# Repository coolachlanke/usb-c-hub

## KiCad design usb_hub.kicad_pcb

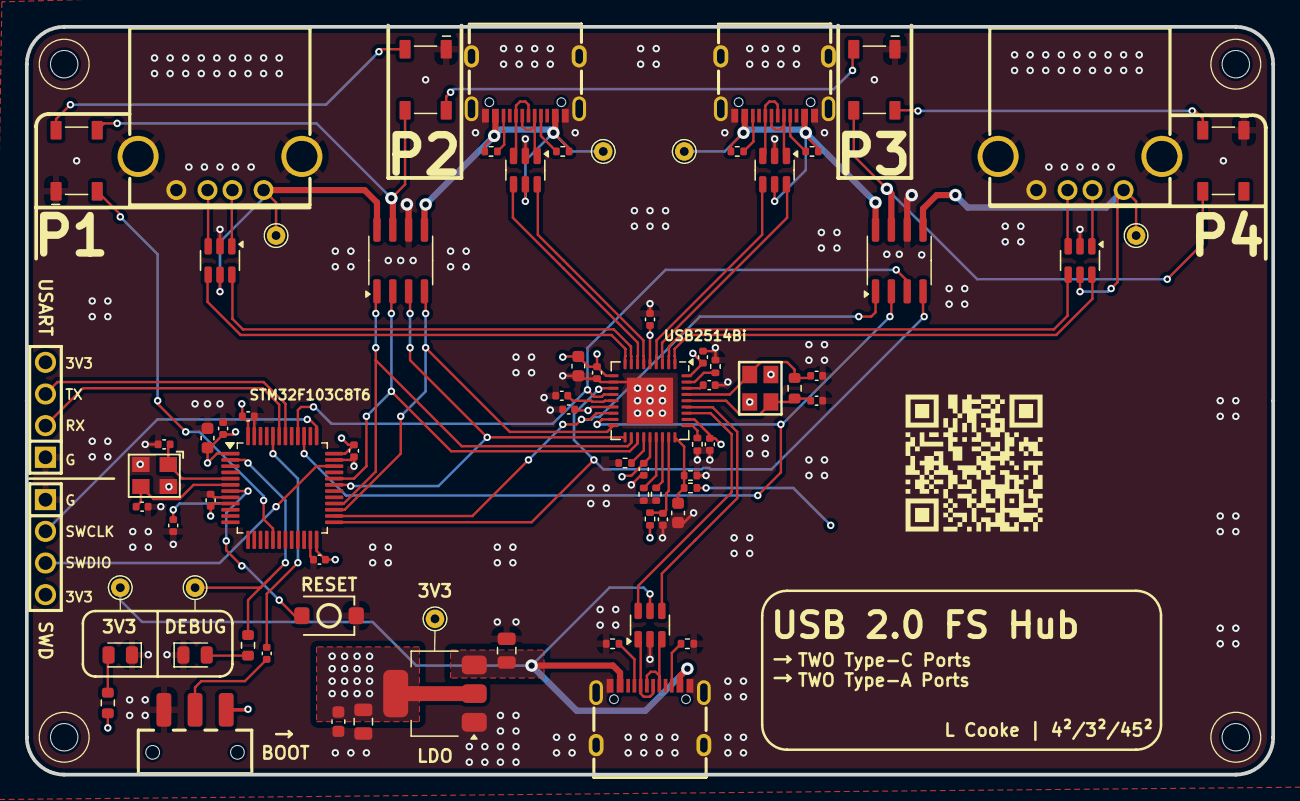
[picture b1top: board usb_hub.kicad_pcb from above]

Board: 4 copper layers, 100.0 x 60.0 mm, 81 parts (0 on the bottom side), 68 nets.

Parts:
C1: 100n; C_0603_1608Metric
C2, C10: 18p; C_0402_1005Metric
C3, C4, C5, C6, C9, C11, C14, C16, C17, C18, C19, C20, C21, C22, C23: 100n; C_0402_1005Metric
C7, C8: 1u; C_0603_1608Metric
C12, C13: 22u; C_0805_2012Metric
C15: 10u; C_0603_1608Metric
C24, C25: 10p; C_0402_1005Metric
D1: GREEN; LED_0805_2012Metric
D2: YELLOW; LED_0805_2012Metric
D3, D4, D5, D6: WS2812B; LED_WS2812B_PLCC4_5.0x5.0mm_P3.2mm
H1, H2, H3, H4: MountingHole; MountingHole_2.2mm_M2
J1, J2, J3: USB_C_Receptacle_USB2.0_16P; USB-C-SMD_TYPE-C-6PIN-2MD-073
J4, J5: USB_A; USB-A-TH_USB-231-ARY
J7, J8: Conn_01x04_Pin; HDR-TH_4P-P2.54-V-M
R1, R2: 5.1k; R_0402_1005Metric
R3, R8, R12, R13: 56k; R_0402_1005Metric
R4, R6, R7, R11, R14, R15, R16: 100k; R_0402_1005Metric
R5: 750R; R_0603_1608Metric
R9: 1M; R_0603_1608Metric
R10: 12k; R_0402_1005Metric
R17: 10k; C_0402_1005Metric
R18: 1k; R_0603_1608Metric
SW1: SW_SPDT; SW-SMD_K3-1280S-K1
SW2: SW_Push; SW-SMD_L3.9-W3.0-P4.45
TP1, TP2, TP3, TP4, TP5, TP6, TP7: TestPoint; TestPoint_THTPad_D1.5mm_Drill0.7mm
U1: USB2514B_Bi; QFN-36-1EP_6x6mm_P0.5mm_EP3.7x3.7mm
U2: AMS1117-3.3; SOT-223-3_TabPin2
U3, U4, U5, U6, U8: USBLC6-2SC6; SOT-23-6
U7, U9: MIC2026-1YM; SOIC-8_3.9x4.9mm_P1.27mm
U10: STM32F103C8T6; LQFP-48_7x7mm_P0.5mm
Y1: 24MHz; CRYSTAL-SMD_4P-L3.2-W2.5-BL_SIT8008BI
Y2: 16MHz; OSC-SMD_4P-L3.2-W2.5-BL

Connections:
+3V3: C1.1, C3.1, C4.1, C5.1, C6.1, C7.1, C13.1, C15.1, C16.1, C17.1, C18.1, C19.1, C20.1, C21.1, C22.1, J7.4, J8.4, R5.1, R11.2, SW1.1 (A), TP2.1, U1.5 (VDDA33), U1.10 (VDDA33), U1.15 (VDD33), U1.23 (VDD33), U1.29 (VDDA33), U1.36 (VDDA33), U2.2 (VO), U10.1 (VBAT), U10.9 (VDDA), U10.24 (VDD), U10.36 (VDD), U10.48 (VDD)
/BOOT0: R17.2, U10.44 (BOOT0)
/DEBUG: R18.1, TP5.1, U10.2 (PC13)
/DEBUG_LED: D2.2 (A), R18.2
/DOWN_1_D+: U1.2 (USBDP_DN1/PRT_DIS_P1), U8.4 (I/O2)
/DOWN_1_D-: U1.1 (USBDM_DN1/PRT_DIS_M1), U8.6 (I/O1)
/DOWN_2_D+: U1.4 (USBDP_DN2/PRT_DIS_P2), U5.4 (I/O2)
/DOWN_2_D-: U1.3 (USBDM_DN2/PRT_DIS_M2), U5.6 (I/O1)
/DOWN_3_D+: U1.7 (USBDP_DN3/PRT_DIS_P3), U4.4 (I/O2)
/DOWN_3_D-: U1.6 (USBDM_DN3/PRT_DIS_M3), U4.6 (I/O1)
/DOWN_4_D+: U1.9 (USBDP_DN4/PRT_DIS_P4), U6.4 (I/O2)
/DOWN_4_D-: U1.8 (USBDM_DN4/PRT_DIS_M4), U6.6 (I/O1)
/EN1: U1.12 (PRTPWR1/BC_EN1), U7.4 (ENB), U10.25 (PB12)
/EN2: U1.16 (PRTPWR2/BC_EN2), U7.1 (ENA), U10.26 (PB13)
/EN3: U1.18 (PRTPWR3/BC_EN3), U9.4 (ENB), U10.27 (PB14)
/EN4: U1.20 (PRTPWR4/BC_EN4), U9.1 (ENA), U10.28 (PB15)
/HSE_IN: C24.1, U10.5 (PD0), Y2.1
/HSE_OUT: C25.1, U10.6 (PD1), Y2.3
/LED_DATA: D3.4 (DIN), U10.17 (PA7)
/NRST: C23.1, SW2.2, U10.7 (NRST)
/OCS_N1: U1.13 (OCS_N1), U7.3 (FLGB), U10.40 (PB4)
/OCS_N2: U1.17 (OCS_N2), U7.2 (FLGA), U10.39 (PB3)
/OCS_N3: U1.19 (OCS_N3), U9.3 (FLGB), U10.31 (PA10)
/OCS_N4: U1.21 (OCS_N4), U9.2 (FLGA), U10.32 (PA11)
/PWR_LED: D1.2 (A), R5.2
/SWCLK: J8.2, U10.37 (PA14)
/SWDIO: J8.3, U10.34 (PA13)
/SW_BOOT0: R17.1, SW1.2 (B)
/UP_D+: U1.31 (USBDP_UP), U3.4 (I/O2)
/UP_D-: U1.30 (USBDM_UP), U3.6 (I/O1)
/USART_RX: J7.2, U10.43 (PB7)
/USART_TX: J7.3, U10.42 (PB6)
GND: C1.2, C2.2, C3.2, C4.2, C5.2, C6.2, C7.2, C8.2, C9.2, C10.2, C11.2, C12.2, C13.2, C14.2, C15.2, C16.2, C17.2, C18.2, C19.2, C20.2, C21.2, C22.2, C23.2, C24.2, C25.2, D1.1 (K), D2.1 (K), D3.3 (VSS), D4.3 (VSS), D5.3 (VSS), D6.3 (VSS), J1.A1 (GND), J1.S1 (SHIELD), J2.A1 (GND), J2.S1 (SHIELD), J3.A1 (GND), J3.S1 (SHIELD), J4.4 (GND), J4.5 (Shield), J5.4 (GND), J5.5 (Shield), J7.1, J8.1, R1.2, R2.2, R4.1, R6.1, R10.1, R14.1, R15.1, R16.1, SW1.3 (C), SW2.1, U1.11 (TEST), U1.37 (VSS), U2.1 (GND), U3.2 (GND), U4.2 (GND), U5.2 (GND), U6.2 (GND), U7.6 (GND), U8.2 (GND), U9.6 (GND), U10.8 (VSSA), U10.23 (VSS), U10.35 (VSS), U10.47 (VSS), Y1.2, Y1.4, Y2.2, Y2.4
unnamed: D3.2 (DOUT), D4.4 (DIN)
unnamed: D4.2 (DOUT), D5.4 (DIN)
unnamed: D5.2 (DOUT), D6.4 (DIN)
unnamed: J1.A5 (CC1), R1.1
unnamed: J1.B5 (CC2), R2.1
unnamed: J1.A6 (D+), J1.B6 (D+), U3.3 (I/O2)
unnamed: J1.A7 (D-), J1.B7 (D-), U3.1 (I/O1)
unnamed: J2.A5 (CC1), R12.1
unnamed: J2.B5 (CC2), R13.1
unnamed: J2.A6 (D+), J2.B6 (D+), U4.3 (I/O2)
unnamed: J2.A7 (D-), J2.B7 (D-), U4.1 (I/O1)
unnamed: J3.A5 (CC1), R3.1
unnamed: J3.B5 (CC2), R8.1
unnamed: J3.A6 (D+), J3.B6 (D+), U5.3 (I/O2)
unnamed: J3.A7 (D-), J3.B7 (D-), U5.1 (I/O1)
unnamed: J4.3 (D+), U6.3 (I/O2)
unnamed: J4.2 (D-), U6.1 (I/O1)
unnamed: J5.3 (D+), U8.3 (I/O2)
unnamed: J5.2 (D-), U8.1 (I/O1)
unnamed: C11.1, U1.14 (CRFILT)
unnamed: R4.2, U1.25 (HS_IND/CFG_SEL1)
unnamed: C9.1, U1.34 (PLLFILT)
unnamed: R10.2, U1.35 (RBIAS)
unnamed: C14.1, R11.1, U1.26 (RESET_N)
unnamed: R16.2, U1.24 (SCL/SMBCLK/CFG_SEL0)
unnamed: R15.2, U1.22 (SDA/SMBDATA/NON_REM1)
unnamed: R14.2, U1.28 (SUSP_IND/LOCAL_PWR/NON_REM0)
unnamed: C8.1, R6.2, R7.1, U1.27 (VBUS_DET)
unnamed: C10.1, R9.2, U1.33 (XTALIN/CLKIN), Y1.1
unnamed: C2.1, R9.1, U1.32 (XTALOUT), Y1.3
VBUS: C12.1, D3.1 (VDD), D4.1 (VDD), D5.1 (VDD), D6.1 (VDD), J1.A4 (VBUS), R7.2, TP1.1, U2.3 (VI), U3.5 (VBUS), U7.7 (IN), U9.7 (IN)
VBUS_1: J5.1 (VBUS), TP7.1, U7.5 (OUTB), U8.5 (VBUS)
VBUS_2: J3.A4 (VBUS), R3.2, R8.2, TP4.1, U5.5 (VBUS), U7.8 (OUTA)
VBUS_3: J2.A4 (VBUS), R12.2, R13.2, TP3.1, U4.5 (VBUS), U9.5 (OUTB)
VBUS_4: J4.1 (VBUS), TP6.1, U6.5 (VBUS), U9.8 (OUTA)

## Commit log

2025-09-14 Initial commit into correct repository
2025-09-14 Added .gitignore
2025-09-14 .gitignore kinda cleanup
2025-09-14 Finished schematic
2025-09-14 Significant work on pcb
2025-09-15 Significant work on pcb again
2025-09-16 Board finished, sending out for fab
2025-09-18 Fixed erroneous LSCS part number (0603 instead of 0402)
